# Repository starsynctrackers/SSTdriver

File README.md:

Schematic Based on the following:

1. BigEasyDriver_v12 by Brian Schmatz
    * [http://www.schmalzhaus.com/BigEasyDriver/](http://www.schmalzhaus.com/BigEasyDriver/)
    * License CC 3.0 Attribution US [https://creativecommons.org/licenses/by/3.0/us/](https://creativecommons.org/licenses/by/3.0/us/)
2. Metro THM+LDO Rv B by Limor Fried & KTOWN
    * [https://github.com/adafruit/Adafruit-METRO-328-PCB](https://github.com/adafruit/Adafruit-METRO-328-PCB)
> For more details, check out the product page at
>
>  * [https://www.adafruit.com/products/2466](https://www.adafruit.com/products/2466)
>
>Designed by Adafruit Industries.  
>Creative Commons Attribution, Share-Alike license, 
>Derivative of "Arduino UNO R3 Reference design" (http://www.arduino.cc/en/Main/ArduinoBoardUno)

### See Also ###
* "[Arduino From Scratch](https://rheingoldheavy.com/category/education/fundamentals/arduino-from-scratch-series/)" by RheinGold Heavy

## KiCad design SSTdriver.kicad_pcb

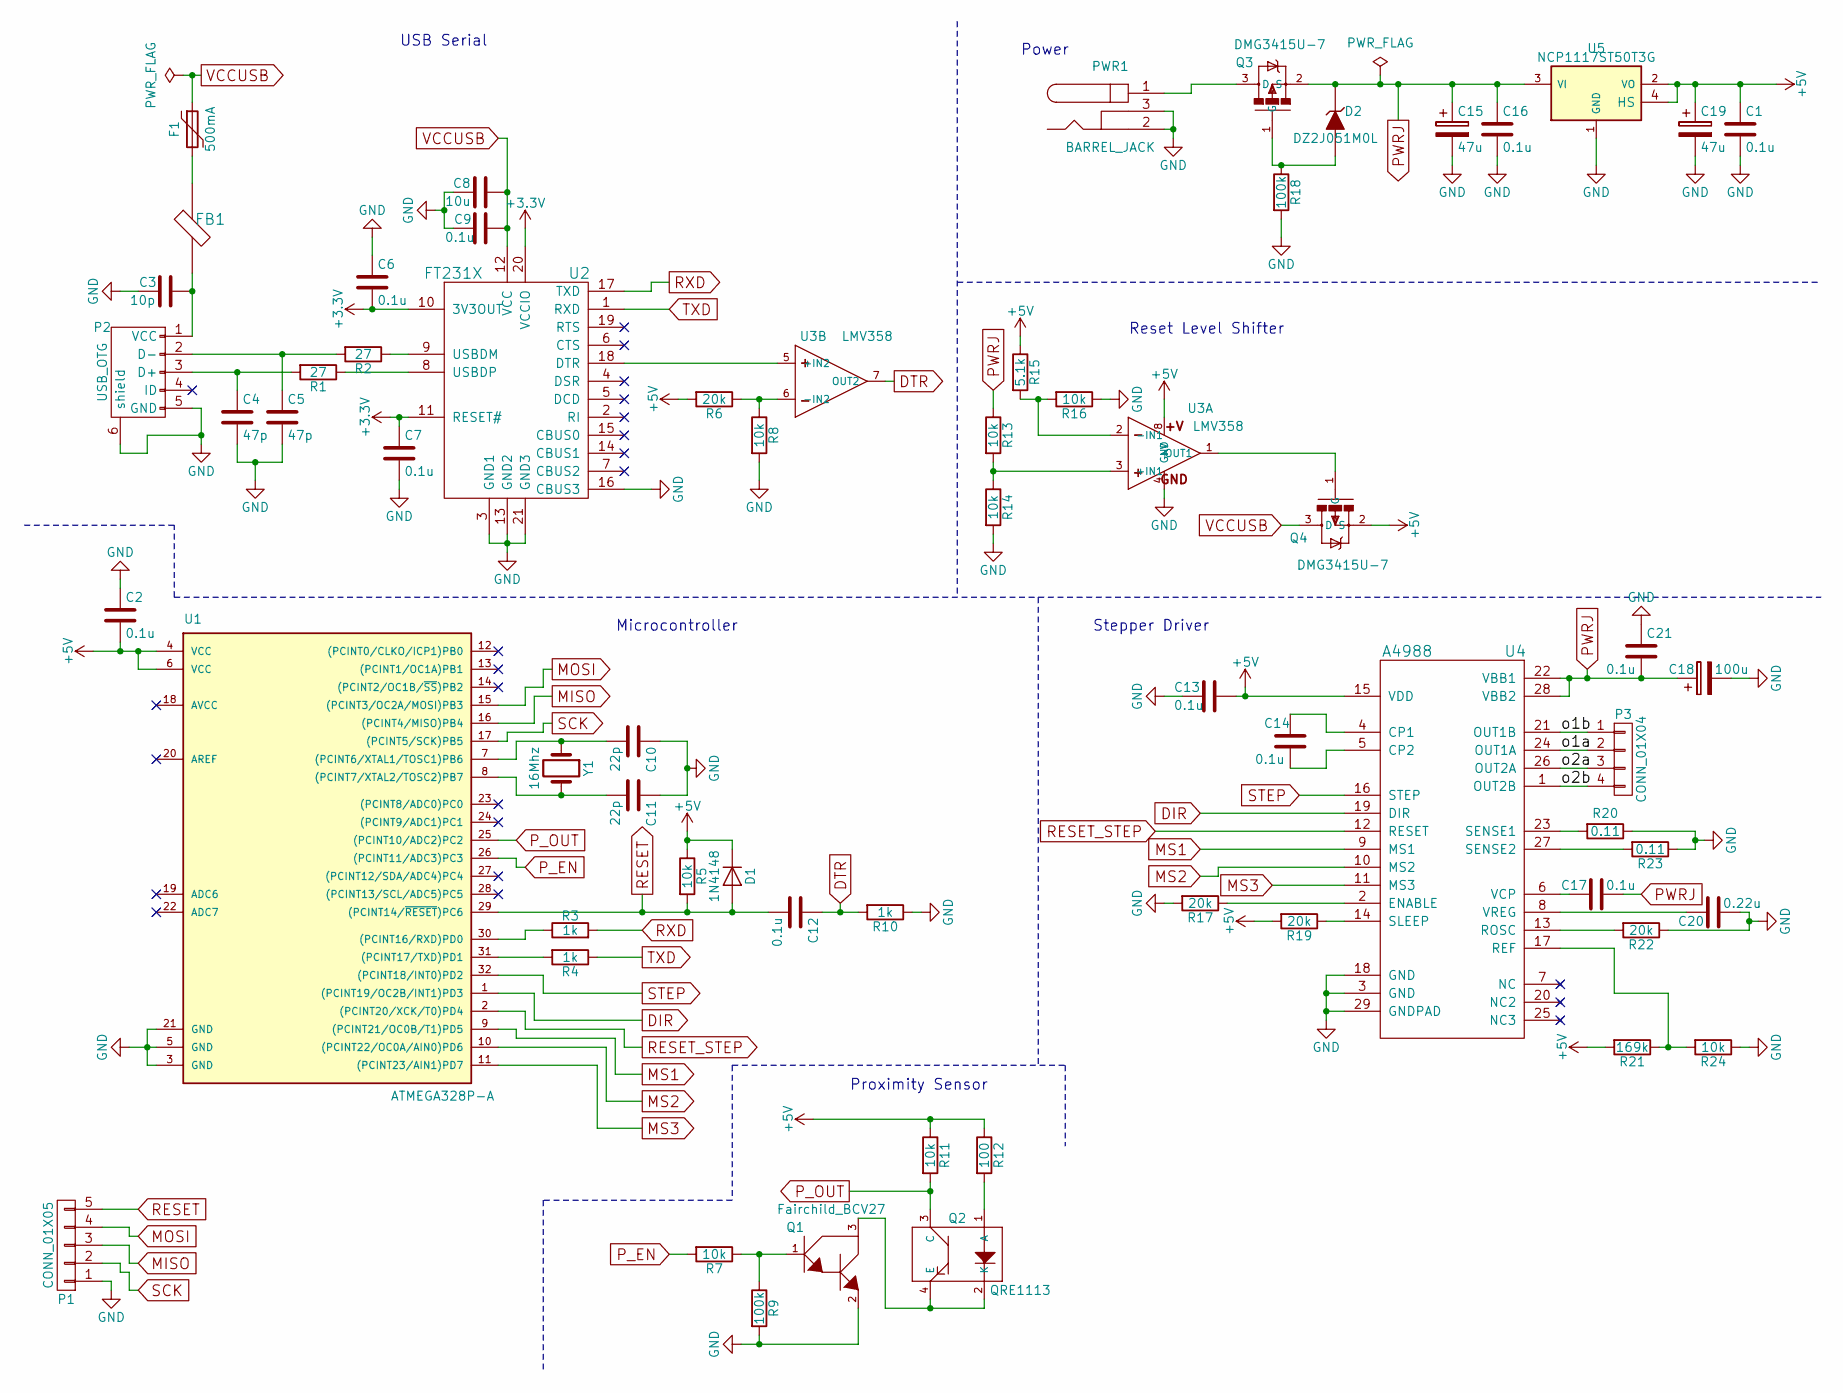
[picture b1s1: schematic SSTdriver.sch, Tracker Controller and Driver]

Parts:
C1, C2, C6, C7, C9, C12, C13, C14, C16, C17, C21: 0.1u; C_0603
C3: 10p; C_0603
C4, C5: 47p; C_0603
C8: 10u; C_0603
C10, C11: 22p; C_0603
C15, C19: 47u; CP_Elec_6.3x5.8
C18: 100u; c_elec_8x10
C20: 0.22u; C_0603
D1: 1N4148; SOD-323
D2: DZ2J051M0L; SOD-323
F1: 500mA; R_1812
FB1: ferrite_bead; R_0805
P1: CONN_01X05; 1X05_LOCK_LONGPADS
P2: USB_OTG; USB-MINIB
P3: CONN_01X04; 1X04_LOCK_LONGPADS
PWR1: BARREL_JACK; POWER_JACK_PTH
Q1: Fairchild_BCV27; SOT-23
Q2: QRE1113; SparkFun-QRE1113
Q3, Q4: DMG3415U-7; SOT-23
R1, R2: 27; R_0603
R3, R4, R10: 1k; R_0603
R5, R7, R8, R11, R13, R14, R16, R24: 10k; R_0603
R6, R17, R19, R22: 20k; R_0603
R9, R18: 100k; R_0603
R12: 100; R_0603
R15: 5.1k; R_0603
R20, R23: 0.11; R_0603
R21: 169k; R_0603
U1: ATMEGA328P-A; TQFP-32_7x7mm_Pitch0.8mm
U2: FT231X; QFN-20-1EP_4x4mm_Pitch0.5mm
U3: LMV358; TSSOP-8_3x3mm_Pitch0.65mm
U4: A4988; QFN-28-1EP_5x5mm_Pitch0.5mm
U5: NCP1117ST50T3G; SOT-223
Y1: 16Mhz; Crystal_HC49-SD_SMD

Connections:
+3V3: C6.2, C7.1, U2.10 (3V3OUT), U2.11 (RESET#), U2.20 (VCCIO)
+5V: C1.1, C2.2, C13.1, C19.1, D1.1 (K), Q4.2 (S), R5.1, R6.2, R11.1, R12.1, R15.1, R19.2, R21.2, U1.4 (VCC), U1.6 (VCC), U3.8 (+V), U4.15 (VDD), U5.2 (VO), U5.4 (HS)
/o1a: P3.2, U4.24 (OUT1A)
/o1b: P3.1, U4.21 (OUT1B)
/o2a: P3.3, U4.26 (OUT2A)
/o2b: P3.4, U4.1 (OUT2B)
DIR: U1.1 ((PCINT19/OC2B/INT1)PD3), U4.19 (DIR)
DTR: C12.1, R10.2, U3.7 (OUT2)
GND: C1.2, C2.1, C3.2, C4.2, C5.2, C6.1, C7.2, C8.1, C9.2, C10.1, C11.1, C13.2, C15.2, C16.2, C18.2, C19.2, C20.1, C21.1, P1.1, P2.5 (GND), P2.6 (shield), PWR1.2, PWR1.3, Q1.2, R8.2, R9.2, R10.1, R14.2, R16.1, R17.2, R18.2, R20.1, R22.1, R23.1, R24.1, U1.3 (GND), U1.5 (GND), U1.21 (GND), U2.3 (GND1), U2.13 (GND2), U2.16 (CBUS3), U2.21 (GND3), U3.4 (GND), U4.3 (GND), U4.18 (GND), U4.29 (GNDPAD), U5.1 (GND)
MISO: P1.3, U1.16 ((PCINT4/MISO)PB4)
MOSI: P1.4, U1.15 ((PCINT3/OC2A/MOSI)PB3)
MS1: U1.9 ((PCINT21/OC0B/T1)PD5), U4.9 (MS1)
MS2: U1.10 ((PCINT22/OC0A/AIN0)PD6), U4.10 (MS2)
MS3: U1.11 ((PCINT23/AIN1)PD7), U4.11 (MS3)
unnamed: C3.1, FB1.2, P2.1 (VCC)
unnamed: C4.1, P2.3 (D+), R1.2
unnamed: C5.1, P2.2 (D-), R2.2
unnamed: C10.2, U1.7 ((PCINT6/XTAL1/TOSC1)PB6), Y1.1
unnamed: C11.2, U1.8 ((PCINT7/XTAL2/TOSC2)PB7), Y1.2
unnamed: C14.1, U4.4 (CP1)
unnamed: C14.2, U4.5 (CP2)
unnamed: C17.2, U4.6 (VCP)
unnamed: C20.2, U4.8 (VREG)
unnamed: D2.2 (A), Q3.1 (G), R18.1
unnamed: F1.2, FB1.1
unnamed: PWR1.1, Q3.3 (D)
unnamed: Q1.1, R7.1, R9.1
unnamed: Q1.3, Q2.2 (K), Q2.4 (E)
unnamed: Q2.1 (A), R12.2
unnamed: Q4.1 (G), U3.1 (OUT1)
unnamed: R1.1, U2.8 (USBDP)
unnamed: R2.1, U2.9 (USBDM)
unnamed: R3.1, U1.30 ((PCINT16/RXD)PD0)
unnamed: R4.2, U1.31 ((PCINT17/TXD)PD1)
unnamed: R6.1, R8.1, U3.6 (-IN2)
unnamed: R13.2, R14.1, U3.3 (+IN1)
unnamed: R15.2, R16.2, U3.2 (-IN1)
unnamed: R17.1, U4.2 (ENABLE)
unnamed: R19.1, U4.14 (SLEEP)
unnamed: R20.2, U4.23 (SENSE1)
unnamed: R21.1, R24.2, U4.17 (REF)
unnamed: R22.2, U4.13 (ROSC)
unnamed: R23.2, U4.27 (SENSE2)
unnamed: U2.18 (DTR), U3.5 (+IN2)
PWRJ: C15.1, C16.1, C17.1, C18.1, C21.2, D2.1 (K), Q3.2 (S), R13.1, U4.22 (VBB1), U4.28 (VBB2), U5.3 (VI)
P_EN: R7.2, U1.26 ((PCINT11/ADC3)PC3)
P_OUT: Q2.3 (C), R11.2, U1.25 ((PCINT10/ADC2)PC2)
RESET: C12.2, D1.2 (A), P1.5, R5.2, U1.29 ((PCINT14/~RESET~)PC6)
RESET_STEP: U1.2 ((PCINT20/XCK/T0)PD4), U4.12 (RESET)
RXD: R3.2, U2.17 (TXD)
SCK: P1.2, U1.17 ((PCINT5/SCK)PB5)
STEP: U1.32 ((PCINT18/INT0)PD2), U4.16 (STEP)
TXD: R4.1, U2.1 (RXD)
VCCUSB: C8.2, C9.1, F1.1, Q4.3 (D), U2.12 (VCC)

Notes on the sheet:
Reset Level Shifter
Power
USB Serial
Microcontroller
Proximity Sensor
Stepper Driver

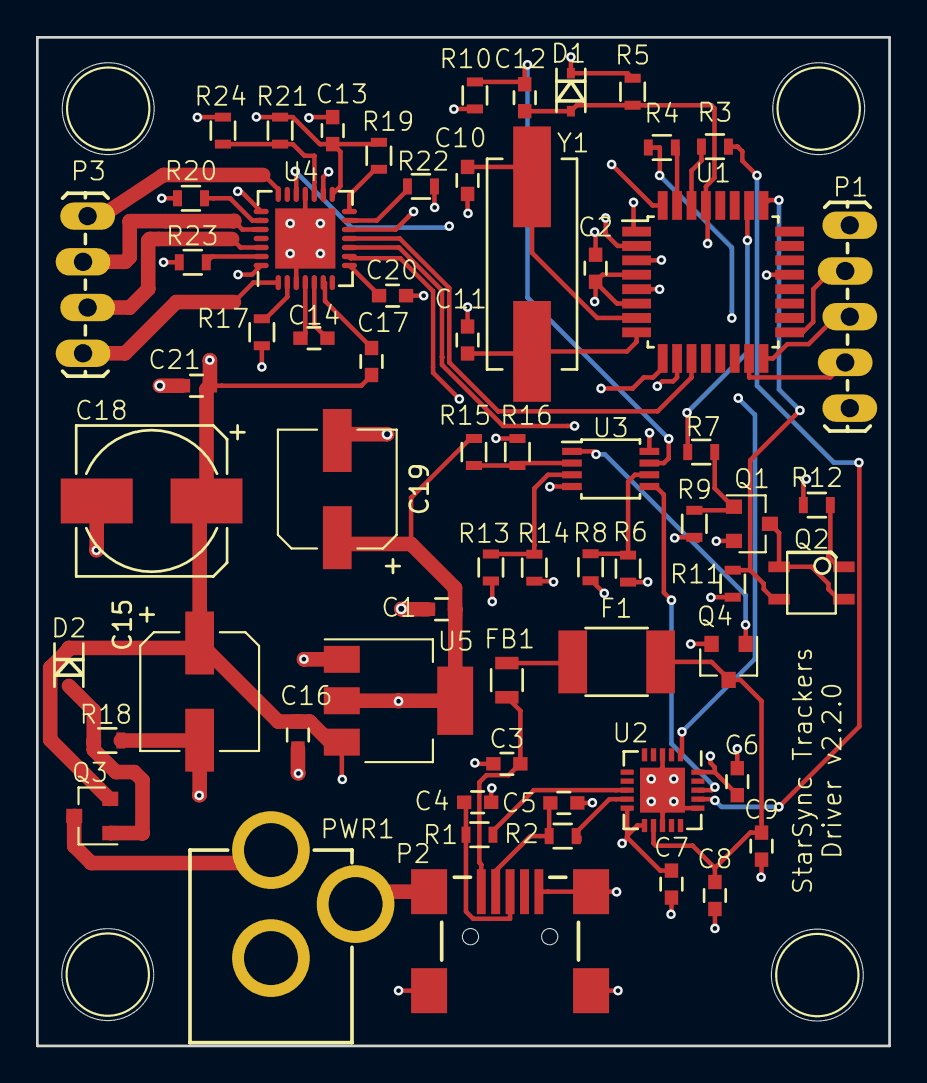
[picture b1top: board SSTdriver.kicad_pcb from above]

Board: 4 copper layers, 47.3 x 56.0 mm, 63 parts (0 on the bottom side), 54 nets.

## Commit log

2017-01-29 First commit of new SSTdriver board.
2018-01-16 Fixed a trace clearance by usb interface chip.
2020-04-24 2.2.0
